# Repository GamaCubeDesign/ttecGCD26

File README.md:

# ttecGCD26 — TT&C, OBC, payload ADS-B e ground station

Repositório da Gama Cube Design para a **CubeDesign 2026**: o software de voo
do Cubetschek (telecomunicação, computador de bordo e payload ADS-B), a
ground station e a documentação de arquitetura.

O hardware: uma Raspberry Pi Zero 2 W a bordo; um rádio LoRa SX1278 (módulo
RA-02) em 433,92 MHz de cada lado do enlace; um SDR NooElec NESDR Nano 3 para
o ADS-B em 1090 MHz; e uma ESP32 DevKit V1 como ground station.

## O número que governa tudo

O enlace LoRa desce **58 KB** nos 10 minutos da missão; 20 aviões geram
**7,34 MiB** de ADS-B bruto no mesmo tempo. É uma diferença de 129 vezes, e
ela obriga o satélite a decodificar e agregar a bordo: ele desce retratos
das aeronaves, com 20 bytes cada, em vez do fluxo bruto. Quase toda a
arquitetura sai daí (`docs/budgets/data-budget.md`, ADR-0003).

## O que tem aqui

| Diretório | O quê | Roda em | Estado em 03/11 |
|---|---|---|---|
| `common/` | O codec compartilhado: frames, CRC, telemetria, telecomandos, IPC, perfis LoRa, o lado da ground do protocolo, os frames do AOCS | Pi, PC **e** ESP32 | pronto |
| `flight/ttcd/` | Telecomunicação: o enlace, os telecomandos, a telemetria; o centro da comunicação entre os processos | Pi | pronto; bancada de 09/10 no protocolo v1 |
| `flight/radio/` | Driver do SX1278 e os rádios real e simulado (UDP) | Pi | pronto |
| `flight/libipc/` | Transporte IPC entre os processos de bordo | Pi | pronto |
| `flight/adsbd/` | Payload ADS-B: supervisiona o `dump1090-fa`, grava o registro de bordo e manda retratos ao `ttcd` | Pi | pronto; com o SDR em 09/10 |
| `flight/obcd/` | Computador de bordo: modos da missão, burn-wire, termostato, sensores da bateria, o I²C emprestado ao AOCS | Pi | pronto; **nunca rodou em hardware** |
| `flight/conf/obc-v2/` | A configuração de voo da placa nova do OBC | Pi | pronta; conferida contra os layouts |
| `ground/console/` | O console da ground station, o mesmo no PC e na ESP32 | Pi, PC, ESP32 | pronto |
| `ground/esp32/` | Firmware da ground station (ESP-IDF, no Docker); `ground/esp32-tests/` roda as suítes portáveis na ESP32 | ESP32 | compila; passa no QEMU; **nunca rodou na placa** |
| `ground/host/` | No PC: a ponte serial da ESP32 (`gs_serial.py`), o adaptador do downlink e o estimador de origem e destino | PC | pronto |
| `tools/` | `gs_cli` (ground de bancada), roteiros da bancada, simulador do `dump1090`, análise, ESP32, CI | Pi, PC | pronto |
| `hardware/` | Fontes KiCad das placas fabricadas e das revisões novas, não fabricadas (`-v2`) | — | — |
| `docs/` | ADRs, orçamentos, ICD do AOCS, requisitos, CDR, relatórios, evidência da bancada | — | — |
| `ultima_missao/` | Código da competição anterior, **congelado**, só referência | — | — |

O software do OBC é escrito aqui desde 20/10/2026. O repositório da outra
equipe (`../obc`) ficou congelado como referência.

## Arquitetura em uma figura

```
 CUBESAT · Raspberry Pi Zero 2 W                              GROUND STATION
 ┌──────────────────────────────────────────────────┐      ┌─────────────────────────┐
 │ [NESDR] ─USB─► dump1090-fa ─TCP :30003 (SBS-1)─┐  │      │ [RA-02] ─SPI─► ESP32    │
 │                                                ▼  │      │   ▲              │ USB  │
 │  adsb.ndjson ◄─ grava ─ adsbd                     │      │   │              ▼      │
 │                          │ IPC                    │      │   │        gs_serial.py │
 │                          ▼                        │      │   │              │ JSON │
 │  [RA-02] ◄─SPI+DIO0─ ttcd ◄──IPC──► obcd          │      │   │              ▼      │
 │     ▲                               │             │      │   │       tracks_to_    │
 │     │      INA219 ◄──I²C1 (dividido)┤             │      │   │       ndjson.py     │
 │     │      ESP32 do AOCS ◄──────────┤             │      │   │              ▼      │
 │     │      DS18B20 ◄─1-Wire─────────┤             │      │   │       estimador e   │
 │     │      burn-wire, aquecedores ◄─┘ GPIO        │      │   │       painel        │
 └─────┼─────────────────────────────────────────────┘      └───┼─────────────────────┘
       └──────────────────── LoRa 433,92 MHz ───────────────────┘
```

- O `ttcd` é o centro: o `adsbd` e o `obcd` se conectam a ele por um socket
  `AF_UNIX`, com os mesmos frames do rádio (ADR-0005, ADR-0006).
- Cada processo tem um núcleo sem chamadas de sistema, testado com relógio
  virtual, e uma casca `epoll` que fala com o sistema operacional.
- O modo da missão, decidido pelo `obcd`, liga a telemetria do `ttcd` e o
  decodificador do `adsbd` (ADR-0014).

O guia de estudo (`docs/relatorios/2026-10-31-guia-de-estudo.html`) explica a
arquitetura, os protocolos e cada arquivo.

## Build e testes

```bash
make                  # configura e compila (CMake, em build/)
make test             # as 38 suítes; make test T=obcd roda só as que casam
make check            # antes de qualquer merge: testes, sanitizers, zero warnings, citações
make check-debian     # o mesmo num contêiner Debian 13, com o GCC 14 da Pi (é o que a CI roda)
make help             # todos os alvos
```

O `make check` roda os testes, compila de novo em `build-asan/` com ASan e
UBSan e com todo warning virando erro, roda os testes ali e confere as
citações de `docs/requisitos.md` contra o regulamento. Na Pi, o segundo build
usa só o UBSan, porque o ASan não inicia no espaço de endereços de 39 bits
dela. Os comandos por baixo (`cmake`, `ctest`, os scripts de `tools/`)
continuam valendo sozinhos.

O build é mantido em **zero warnings** com `-Wall -Wextra -Wpedantic
-Wconversion -Wsign-conversion`. Isso não é cosmético: quase todo bug que este
projeto não pode pagar, um campo de tamanho truncado, um sinal perdido numa
latitude, aparece primeiro como conversão implícita.

A ESP32 compila no Docker, sem instalar o ESP-IDF:

```bash
make esp32-build                          # o firmware da ground
make esp32-tests-qemu                     # as suítes portáveis numa ESP32 emulada
make esp32-flash ESP32_PORT=/dev/ttyUSB0  # grava na placa
```

## Sem hardware, e na bancada

```bash
make bench-ping RADIO=udp                 # um passo da bancada no rádio simulado
make adsb-chain INPUT=<captura.sbs|registro.ndjson>   # uma missão inteira pela cadeia
```

- Para mandar o código do PC para a Pi, os passos da bancada dos rádios e a
  instalação dos serviços, veja `flight/ttcd/README.md`.
- O roteiro da próxima bancada é
  `docs/relatorios/2026-11-03-roteiro-bancada.html`.
- A evidência das bancadas fica em `docs/vv/bancada/`.

## Orçamento de enlace e de dados

Todo número citado nos ADRs sai de um script:

```bash
make budget           # as tabelas completas (tools/analysis/lora_budget.py)
make budget-check     # confere contra os ADRs (também roda no make test)
make boards           # a configuração de voo conferida, fio a fio, contra os layouts das placas
```

## Onde começar a ler

1. `AGENTS.md`: as regras do repositório, o mapa e o estado corrente.
2. O guia de estudo, `docs/relatorios/2026-10-31-guia-de-estudo.html`: do
   conceito ao arquivo.
3. `docs/adr/README.md`: o índice das decisões. Comece pelo ADR-0003 (por que
   o processamento é a bordo) e pelo ADR-0004 (a configuração do rádio, com a
   aritmética).
4. `PLANO.md`: o plano até a prova, as decisões, as questões em aberto e os
   riscos.
5. `docs/requisitos.md`: cada requisito citado literalmente, com o estado.

Os relatórios de estado, datados, ficam em `docs/relatorios/`; o mais recente
é `2026-11-03-status-firmware.html`.

## Convenções

- **Código e comentários: inglês.** ADRs, ICDs e orçamentos também: o
  regulamento (§2) exige o Design Package em inglês, e esses documentos entram
  nele quase literalmente.
- **READMEs, PLANO e notas de trabalho: português.**
- Identificadores de requisito (`HLR-ADS-07` etc.) são citados em comentário
  no ponto do código que os atende; a matriz de rastreabilidade sai daí.
- Nunca serializar struct por cast. Todo campo multi-byte passa pelos helpers
  little-endian de `common/gama_bytes.h`. O porquê está no ADR-0002.

## `ultima_missao/`

O código da competição anterior, **congelado**, mantido só como referência.
O que foi reaproveitado e o que foi descartado está nos ADRs 0002 e 0004, com
o motivo de cada descarte. Os defeitos dele viraram as "regras duras" do
`AGENTS.md`.

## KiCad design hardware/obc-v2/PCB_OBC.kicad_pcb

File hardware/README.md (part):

# Placas do Cubetschek — fontes KiCad

As placas como foram **fabricadas**: as fontes dos dois painéis enviados à
Circuibras em 08/10/2026, trazidas de `PCBS_GCD_Com_Paineis.zip` em
22/10/2026. Uma pasta por placa; cada uma abre no KiCad pelo `.kicad_pro`
(os painéis exigem o KiCad 10). As exceções são as pastas `-v2`, que ainda
não foram fabricadas: `obc-v2/`, a placa nova do OBC, e `eps-potencia-v2/` e
`aocs-v2/`, da revisão TF de 01–02/11 (abaixo). A `antenas/` veio de outro
zip, `PCB_mec.7z` (abaixo).

| Pasta | Placa | Observação |
|---|---|---|
| `obc/` | OBC: Raspberry Pi Zero 2 W, INA219, barramento | revisão de 08/10 (`PCB_NOVAS_REVISADAS/PCB_OBC_NOVA`); esquemático e layout **divergem** no I²C (pinos 10 e 12); a `obc-v2/` a substitui |
| `obc-v2/` | OBC, placa nova | esquemático de 23/10 (`PCB_OBC_NEW.zip`), layout da revisão TF de 02/11; **não fabricada**; corrige A1, A2, A3 e A7 |
| `ttec/` | TT&C: Ra-02, USB do SDR, J4 (JST XH) do burn-wire, para a placa de antenas | bibliotecas locais em `Library.pretty/` e `lib.sym/` |
| `eps-potencia/` | EPS: BMS 2S, conversores de 5 V, 3,3 V e 12 V, entrada externa | revisão de 08/10 (`PCB_NOVAS_REVISADAS/PCB_EPS_EXTRA_NOVA`) |
| `eps-potencia-v2/` | EPS, revisão TF | layout de 02/11, **mesmas ligações** da fabricada; sem esquemático; **não fabricada** |
| `bateria-cima/` | bateria de cima: 18650, aquecedores, TIP120, DS18B20 | |
| `bateria-baixo/` | bateria de baixo: 18650, aquecedores, TIP120 | sem sensor de temperatura |
| `aocs/` | AOCS: ESP32, BMI088, AS5048A, DRV8313 | o esquemático estava em `AOCS/grb/` no zip |
| `aocs-v2/` | AOCS, revisão TF | layout de 02/11, **mesmas ligações** do fabricado; sem esquemático; **não fabricado** |
| `painel-solar-1/`, `painel-solar-2/` | painéis solares | |
| `topo/` | tampa superior | só logotipos, sem componentes |
| `paineis/` | os dois painéis de fabricação, 20 placas cada | ver abaixo |
| `antenas/` | placa de antenas: dipolo de fitas do LoRa, dipolo impresso do ADS-B, os baluns LC e o burn-wire (TIP120), que é a placa do mecanismo | KiCad de 19/10 (`PCB_mec.7z`) e `componentes_baluns.pdf` (valores comerciais dos baluns, co-simulação HFSS); fabricação a confirmar |

A placa do **mecanismo** (burn-wire) é a de antenas: seção `antenas/`, abaixo.

As revisões de 08/10 do OBC e da EPS são as que foram para os painéis
(conferido pelo SHA-256 citado em `paineis/Relatorio_Painelizacao.md`). As
versões anteriores, que ficavam em `OBC/` e `EPS/` no zip, não foram
fabricadas e ficaram de fora. A revisão não mudou nenhuma ligação do
barramento de 40 pinos nas duas placas.

## `obc-v2/` — a placa nova do OBC

O esquemático de `PCB_OBC_NEW.zip` (KiCad de 23/10/2026), a pinagem em uso
desde 31/10, com o layout da revisão TF de 02/11 (seção seguinte; o layout
de 23/10 fica no histórico do git, commit `99adcf1`). Ficaram de fora o
`.history/` e o `.kicad_prl`. Conferida pelo netlist do esquemático e pelos
pads do `.kicad_pcb`, que concordam.

Dos achados de `docs/relatorios/2026-10-22-validacao-obc.html`, corrige:

| Achado | Na placa nova |
|---|---|
| A1: o 8 V passava pelo INA219 em pinos que a EPS não usa | entra do 8 V Bruto no J1.38, onde a EPS o põe, e sai no J1.33; o J1.35 ficou livre |
| A2: o barramento do LoRa trocado com o da TT&C | J1.21 SCK, 23 MISO, 25 MOSI, 27 NSS, 29 RESET, 31 DIO0, como o J3 da TT&C |
| A3: SDA e SCL trocados no layout | J1.10 SDA, J1.12 SCL, como o AOCS |
| A7: DS18B20 sem pull-up | R1, 4,7 kΩ, do 3,3 V à linha do DS18B20 (GPIO17, J1.9) |

Não muda:

- **A5 e A6:** R2 e R3 continuam 4,7 kΩ entre o GPIO e a base dos TIP120
  (GPIO22 → J1.13, burn-wire; GPIO23 → J1.11, aquecedores). Nos aquecedores
  são ~0,43 mA para duas bases. No burn-wire, o R2 fica em série com o 220 Ω
  e o pull-down de 10 kΩ da placa de antenas: ~0,25 mA de base, ~0,25 A
  garantidos com o ganho mínimo de 1000 do TIP120, contra o ~1 A do ensaio
  do CDR. Com o R2 em 470 Ω, a base recebe ~2,6 mA e o TIP120 satura.
- **O INA219 fica no I²C1**, dividido com o ESP32 do AOCS (GPIO2/3, J1.10 e
  J1.12): a proposta de 24/10 de levá-lo ao I²C0 não entrou. O `obcd`
  empresta o barramento ao ESP32 durante o `ADVANCED_AOCS` (ADR-0017).

Pinos da Pi nesta placa:

| Função | GPIO | Barramento (J1) |
|---|---|---|
| LoRa SCK, MISO, MOSI, NSS | 11, 9, 10, 8 (SPI0, CE0) | 21, 23, 25, 27 |
| LoRa RESET, DIO0 | 25, 4 | 29, 31 |
| I²C1 SDA, SCL: INA219 (0x40) e ESP32 do AOCS | 2, 3 | 10, 12 |
| DS18B20 (1-Wire) | 17 | 9 |
| burn-wire, aquecedores (bases dos TIP120) | 22, 23 | 13, 11 |

Com o DIO0 no GPIO4, que é o pino padrão do 1-Wire, o `config.txt` precisa
de `dtoverlay=w1-gpio,gpiopin=17`. A configuração do software para esta
placa está em `flight/conf/obc-v2/`.

## `antenas/` — a placa de antenas e o burn-wire

`PCB_mec.7z`, recebido em 03/11: o projeto `PCB_antenas` da equipe de
antenas, KiCad de 19/10. A placa leva o dipolo de fitas do LoRa (face de
cima), o dipolo impresso do ADS-B (face de baixo) e os baluns LC dos dois.
Desde 19/10 leva também o circuito do burn-wire: é a placa do mecanismo. O
`componentes_baluns.pdf` já estava na pasta.

O burn-wire é o circuito da Figura 15 do CDR:

| JST1 (JST EH) | Na placa de antenas | J4 da TT&C (JST XH) |
|---|---|---|
| 1 | `GND_q`: emissor do TIP120 (Q1) e R1 | GND |
| 2 | furo H14: uma ponta do NiCr | +5V, do J3.15 |
| 3 | R2, 220 Ω, até a base do Q1 | o sinal do J3.13 (GPIO22, pelo R2 de 4,7 kΩ do OBC) |

- R1, de 10 kΩ, vai da base ao emissor: é o pull-down que o achado A8 pedia.
  A outra ponta do NiCr vai no furo H15, o coletor. O NiCr é soldado nos
  furos H14 e H15 (0,8 mm, não metalizados, com anel nas duas faces).
- O cabo liga o J4 ao JST1 pino a pino. XH e EH têm o mesmo passo, mas não
  são intercambiáveis: o cabo leva um alojamento de cada série.
- O ensaio do CDR (§6.4) tinha esse circuito sem o R2 de 4,7 kΩ do OBC:
  ~8,5 mA de base, 1 A a 5 V, pulso de 2 s. Com o 4,7 kΩ em série,
  ~0,25 mA (A5, abaixo).

O DRC (`kicad-cli pcb drc --schematic-parity`) dá 0 violações das regras da
placa (folga de 0,15 mm), 1 aviso de serigrafia e 0 divergências entre o
esquemático e o layout. Os 3 itens "desconectados" são as ligações por fio
soldado à mão, de propósito: o H10, que representa o GND das duas faces
(ligado pelos furos H9–H13), e o H14 e o H15, as pontas do NiCr.

Ficaram de fora o `.history/` e o `.kicad_prl`. Também ficaram de fora, por
serem de 14/10, de antes do burn-wire, a pasta `fabricacao/` (gerbers,
furação, BOM, posição, PDFs, STEP), as `imagens/` e o `README.md` do projeto.
A furação de lá só tem os 4 furos das fitas, e o BOM só os componentes de
RF: os arquivos de fabricação precisam ser gerados de novo a partir do
`.kicad_pcb`. Os `scripts/` que geram a placa a partir do DXF do HFSS (que
não veio no zip) também ficaram de fora: eles não têm o burn-wire, e rodá-los
de novo apaga o circuito.

## A revisão TF (01–02/11/2026)

`PCBS_GAMA_AOCS_EPS1_OBC_TF.zip`, recebido em 03/11: novos layouts do OBC, da
EPS e do AOCS. **Nenhuma ligação mudou.** Comparados pad a pad, pela net de
cada pad no `.kicad_pcb` (`tools/analysis/board_check.py diff`):

- o OBC TF contra o `obc-v2` de 23/10: 0 mudanças; esquemático, `.kicad_pro`
  e `.kicad_dru` idênticos byte a byte;
- a EPS TF contra a `eps-potencia/` fabricada: 0 mudanças;
- o AOCS TF contra o `aocs/` fabricado: 0 mudanças.

O que mudou é o cobre:

| Placa | Trilhas | Vias | Componentes |
|---|---|---|---|
| OBC | re-roteadas, todas de 1 mm: 258 → 206 segmentos | 40 → 33 | nenhum se moveu |
| EPS | todas de 1 mm, como antes: 107 → 98 segmentos | 343 → 37 | a chave SW1 desceu ~7 mm; furos renumerados |
| AOCS | de 0,5 para 1 mm: 115 → 157 segmentos | 391 → 47 | furos renumerados |

O contorno (83 × 83 mm) e os conectores do barramento estão no mesmo lugar:
o empilhamento não muda.

**O DRC do KiCad** (`kicad-cli pcb drc`) não acha nenhum item desconectado
nem curto nas três, mas acha erros que as versões anteriores não tinham. São
para resolver antes de fabricar:

- **OBC:** 5 violações da regra própria `caseira_isolacao_1mm`, com 0,86 a
  0,99 mm de folga. Os pares são as vias DIO0 × NSS e a trilha MOSI × a via
  MISO, do LoRa, e as vias TIP120(CT) × DS18B20. Há também 2 pontas de
  trilha soltas (SCL e DIO0). O `PCB_OBC.kicad_dru` tem dois conjuntos de
  regras: as da Circuibras (folga de 0,127 mm), em que o OBC TF passa, e, no
  fim, as da versão caseira (transferência térmica: folga e trilha de 1 mm),
  que valem por cima. A reunião de 03/11 decidiu que o OBC é feito pela
  equipe, que é justamente o caso da regra caseira. Falta confirmar que o
  processo separa 0,86 mm, e baixar a regra para esse valor, ou afastar os
  três pontos.
- **AOCS:** a trilha do D34 do ESP32 passa a 0,24 mm do pad de GND do
  conector X+, contra os 0,5 mm da classe padrão; a Circuibras faz 0,127 mm,
  então depende de quem fabrica. Há também 6 trilhas com uma
  ponta solta (três delas de ~22 mm, nas entradas IN1–IN3 do DRV8313) e duas
  vias empilhadas no mesmo ponto, no SDA do BMI088.
- **EPS:** só avisos de serigrafia e de footprint.

**Como entraram.** A EPS e o AOCS vieram sem esquemático: o da EPS estava
vazio e ficou de fora, porque um "Update PCB from Schematic" com ele apagaria
todos os componentes. O esquemático que vale para os dois é o da versão
fabricada (`eps-potencia/`, `aocs/`), já que as ligações são as mesmas. O
projeto do AOCS se chamava `AAAAAAAAAAAAAAAAAAAAAAAAAAAAA` no zip e foi
renomeado para `AOCS_TF`. Os footprints estão embutidos nos `.kicad_pcb`; a
biblioteca do AOCS continua em `aocs/`. Os modelos 3D apontam para caminhos
nos computadores dos autores, como nas versões fabricadas.

## O firmware e as pendências de 22/10

`python3 tools/analysis/board_check.py` segue cada fio que o firmware usa, do
GPIO da Pi ao pino do chip na outra placa. Ele lê os layouts do stack
(`obc-v2`, `ttec`, `eps-potencia-v2`, as baterias e `aocs-v2`), a placa de
antenas, ligada à TT&C por um cabo, e a configuração em
`flight/conf/obc-v2/`. Em 03/11 passa em todas as 20 conferências, e roda no
`make test`. Item a item de
`docs/relatorios/2026-10-22-validacao-obc.html`:

| Achado | Nas placas | O firmware |
|---|---|---|
| A1 · 8 V pelo INA219 | corrigido no OBC: entra do 8V(Bruto) da EPS no J1.38, sai no J1.33 para o 8V(Liq) | nada a mudar. Sem a placa do OBC no stack, nada recebe energia (HLR-EPS-05) |
| A2 · barramento do LoRa | corrigido: 21–31 casam com o J3 da TT&C | `ttcd.conf` confere: `spidev0.0`, RESET 25, DIO0 4 |
| A3 · SDA e SCL | corrigido: 10 SDA, 12 SCL no OBC e no AOCS | `obcd.conf` confere: `/dev/i2c-1` |
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
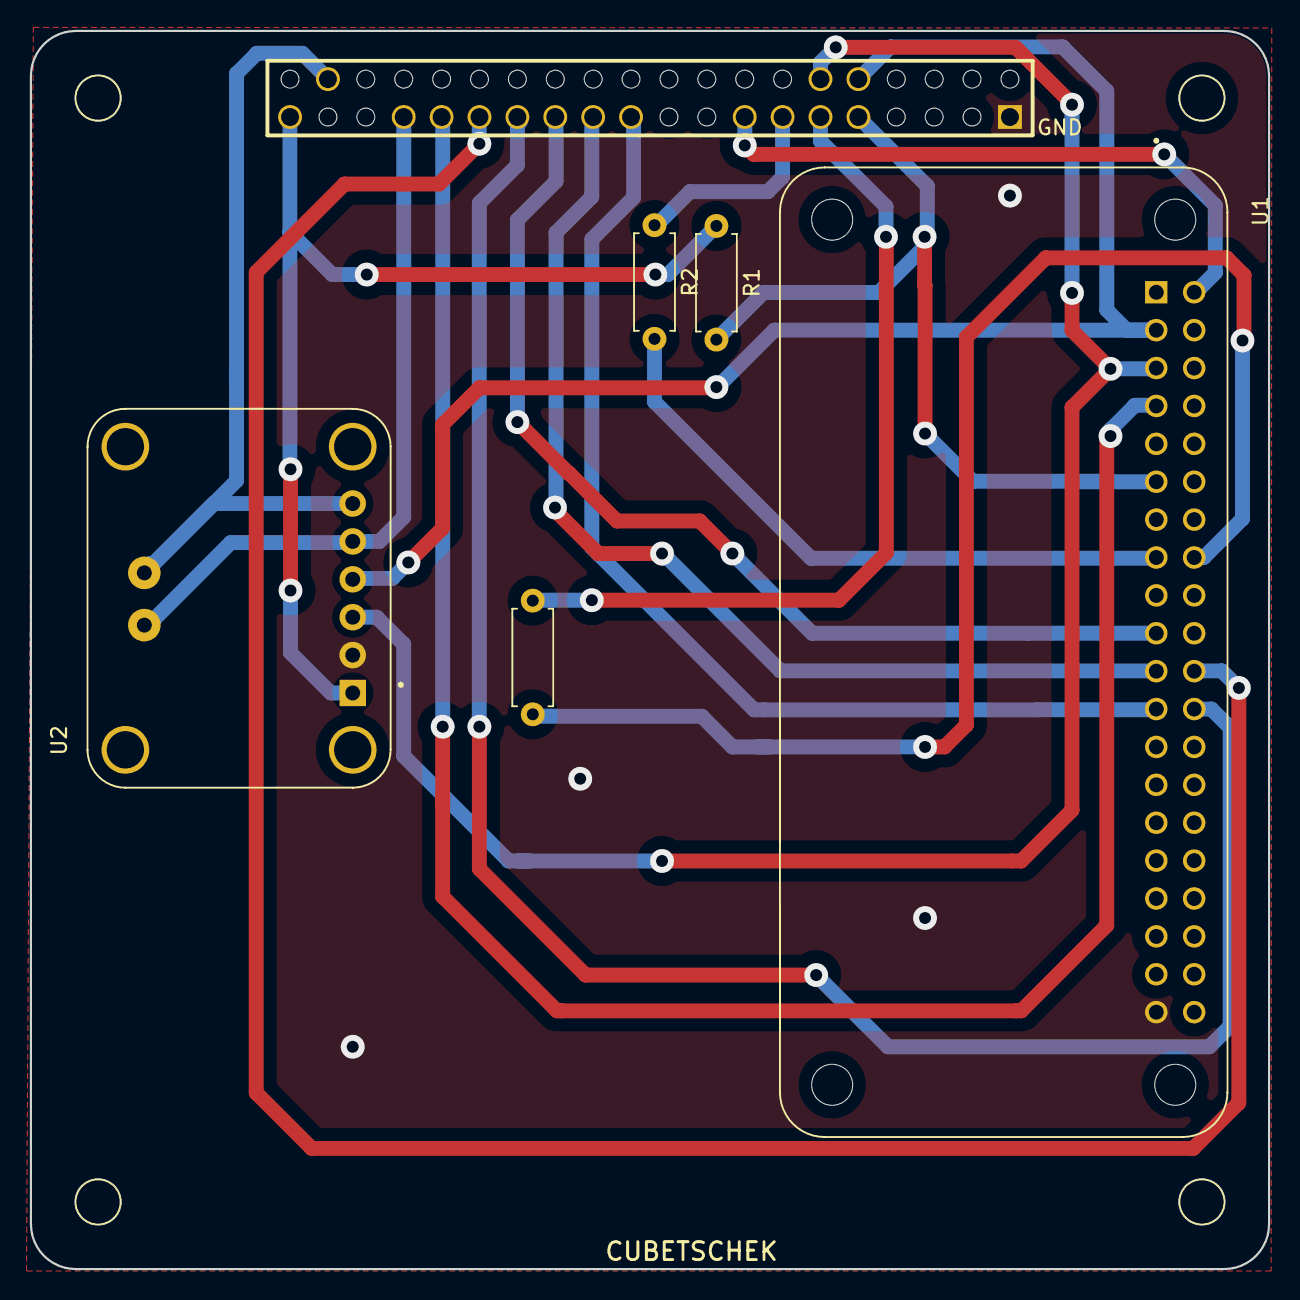
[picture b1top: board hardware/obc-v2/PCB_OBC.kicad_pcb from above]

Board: 2 copper layers, 83.0 x 83.0 mm, 6 parts (0 on the bottom side), 18 nets.

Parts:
J1: PC104_PSTD-2.54-2X20P
R1, R2, R3: 4.7k; R_Axial_DIN0207_L6.3mm_D2.5mm_P7.62mm_Horizontal
U1: RASPBERRY_PI_ZERO_2_W; MODULE_RASPBERRY_PI_ZERO_2_W
U2: INA219; MODULE_INA219

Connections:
/3V3: J1.39, R1.1, U2.1 (VCC)
/5V: J1.15, U1.2 (5V_2)
/8V Bruto: J1.38, U2.6 (VIN+), U2.VIN+
/8V(INA): J1.33, U2.5 (VIN-), U2.VIN-
/DIO0 LORA: J1.31, U1.7 (GPIO4/GPIO_GCLK)
/DS18B20: J1.9, R1.2, U1.11 (GPIO17/GPIO_GEN0)
/GND: J1.1, U1.39 (GND_39), U2.2 (GND)
/MISO LORA: J1.23, U1.21 (GPIO9/SPI_MISO)
/MOSI LORA: J1.25, U1.19 (GPIO10/SPI_MOSI)
/NSS LORA: J1.27, U1.24 (GPIO8/SPI_~CE0)
/RESET LORA: J1.29, U1.22 (GPIO25/GPIO_GEN6)
/SCK LORA: J1.21, U1.23 (GPIO11/SPI_SCLK)
/SCL: J1.12, U1.5 (GPIO3/SCL), U2.3 (SCL)
/SDA: J1.10, U1.3 (GPIO2/SDA1), U2.4 (SDA)
/TIP120(CT): J1.11, R3.2
/TIP120(Mec): J1.13, R2.1
unnamed: R2.2, U1.15 (GPIO22/GPIO_GEN3)
unnamed: R3.1, U1.16 (GPIO23/GPIO_GEN4)

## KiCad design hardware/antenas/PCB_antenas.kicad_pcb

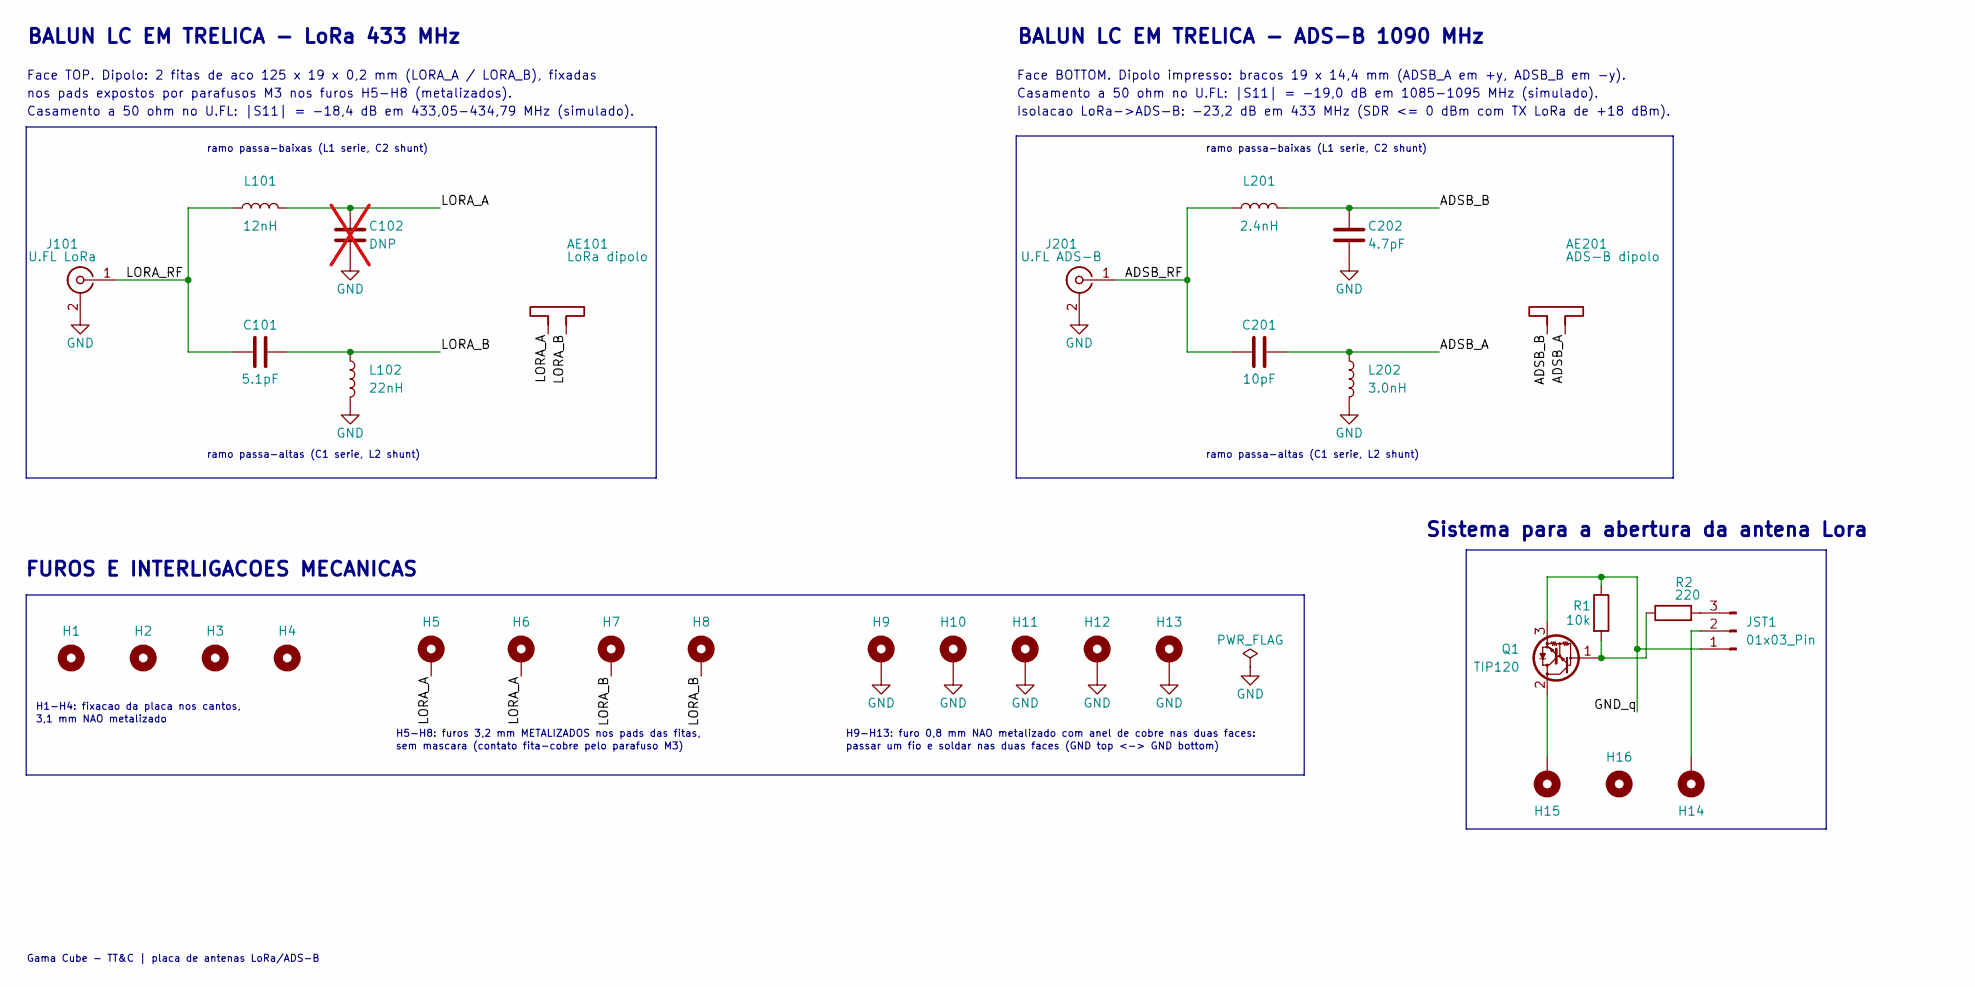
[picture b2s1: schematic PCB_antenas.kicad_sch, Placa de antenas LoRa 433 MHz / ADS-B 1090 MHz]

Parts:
AE101: LoRa dipolo
AE201: ADS-B dipolo
C101: 5.1pF; C_0402_1005Metric
C102: DNP; C_0402_1005Metric; not fitted
C201: 10pF; C_0603_1608Metric
C202: 4.7pF; C_0603_1608Metric
H1, H2, H3, H4, H16: Furo 3,1 NPTH; Furo_Fixacao_3.1mm_NPTH
H5, H6, H7, H8: Furo fita 3,2 PTH; Furo_Fita_3.2mm_PTH
H9, H10, H11, H12, H13, H14, H15: Fio GND; Furo_Fio_GND_0.8mm
J101: U.FL LoRa; U.FL_Hirose_U.FL-R-SMT-1_Vertical_SemJanela
J201: U.FL ADS-B; U.FL_Hirose_U.FL-R-SMT-1_Vertical_SemJanela
JST1: 01x03_Pin; JST_EH_B3B-EH-A_1x03_P2.50mm_Vertical
L101: 12nH; L_0603_1608Metric
L102: 22nH; L_0603_1608Metric
L201: 2.4nH; L_0402_1005Metric
L202: 3.0nH; L_0603_1608Metric
Q1: TIP120; TO-220-3_Vertical
R1: 10k; R_Axial_DIN0207_L6.3mm_D2.5mm_P7.62mm_Horizontal
R2: 220; R_Axial_DIN0207_L6.3mm_D2.5mm_P7.62mm_Horizontal

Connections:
/ADSB_A: AE201.2, C201.2, L202.1
/ADSB_B: AE201.1, C202.1, L201.2
/ADSB_RF: C201.1, J201.1 (In), L201.1
/GND_q: JST1.1, Q1.3 (E), R1.1
/LORA_A: AE101.1, C102.1, H5.1 (1_1), H6.1 (1_1), L101.2
/LORA_B: AE101.2, C101.2, H7.1 (1_1), H8.1 (1_1), L102.1
/LORA_RF: C101.1, J101.1 (In), L101.1
GND: C102.2, C202.2, H9.1 (1_1), H10.1 (1_1), H11.1 (1_1), H12.1 (1_1), H13.1 (1_1), J101.2 (Ext), J201.2 (Ext), L102.2, L202.2
unnamed: H14.1 (1_1), JST1.2
unnamed: JST1.3, R2.2
unnamed: Q1.1 (B), R1.2, R2.1
unnamed: H15.1 (1_1), Q1.2 (C)

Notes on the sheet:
H1-H4: fixacao da placa nos cantos,
BALUN LC EM TRELICA - ADS-B 1090 MHz
ramo passa-altas (C1 serie, L2 shunt)
FUROS E INTERLIGACOES MECANICAS
Isolacao LoRa->ADS-B: -23,2 dB em 433 MHz (SDR <= 0 dBm com TX LoRa de +18 dBm).
Gama Cube - TT&C | placa de antenas LoRa/ADS-B
Casamento a 50 ohm no U.FL: |S11| = -18,4 dB em 433,05-434,79 MHz (simulado).
ramo passa-baixas (L1 serie, C2 shunt)
passar um fio e soldar nas duas faces (GND top <-> GND bottom)
Face TOP. Dipolo: 2 fitas de aco 125 x 19 x 0,2 mm (LORA_A / LORA_B), fixadas
sem mascara (contato fita-cobre pelo parafuso M3)
H5-H8: furos 3,2 mm METALIZADOS nos pads das fitas,
Face BOTTOM. Dipolo impresso: bracos 19 x 14,4 mm (ADSB_A em +y, ADSB_B em -y).
nos pads expostos por parafusos M3 nos furos H5-H8 (metalizados).
Casamento a 50 ohm no U.FL: |S11| = -19,0 dB em 1085-1095 MHz (simulado).
3,1 mm NAO metalizado
BALUN LC EM TRELICA - LoRa 433 MHz
H9-H13: furo 0,8 mm NAO metalizado com anel de cobre nas duas faces:
Sistema para a abertura da antena Lora

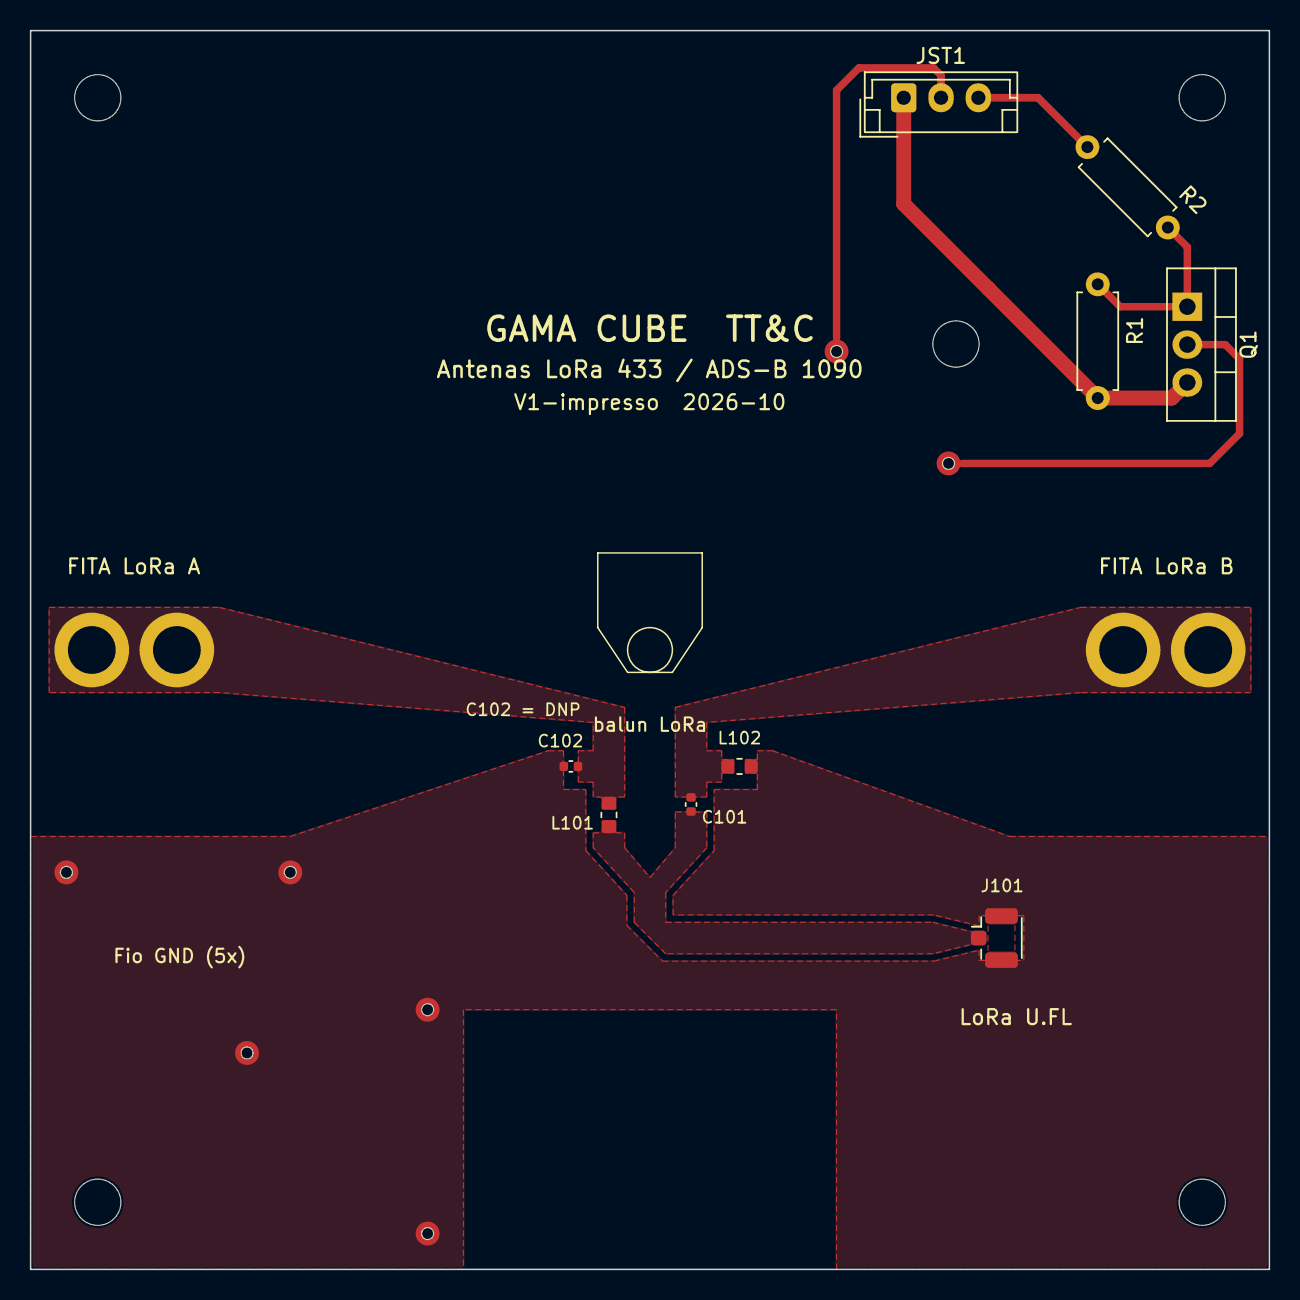
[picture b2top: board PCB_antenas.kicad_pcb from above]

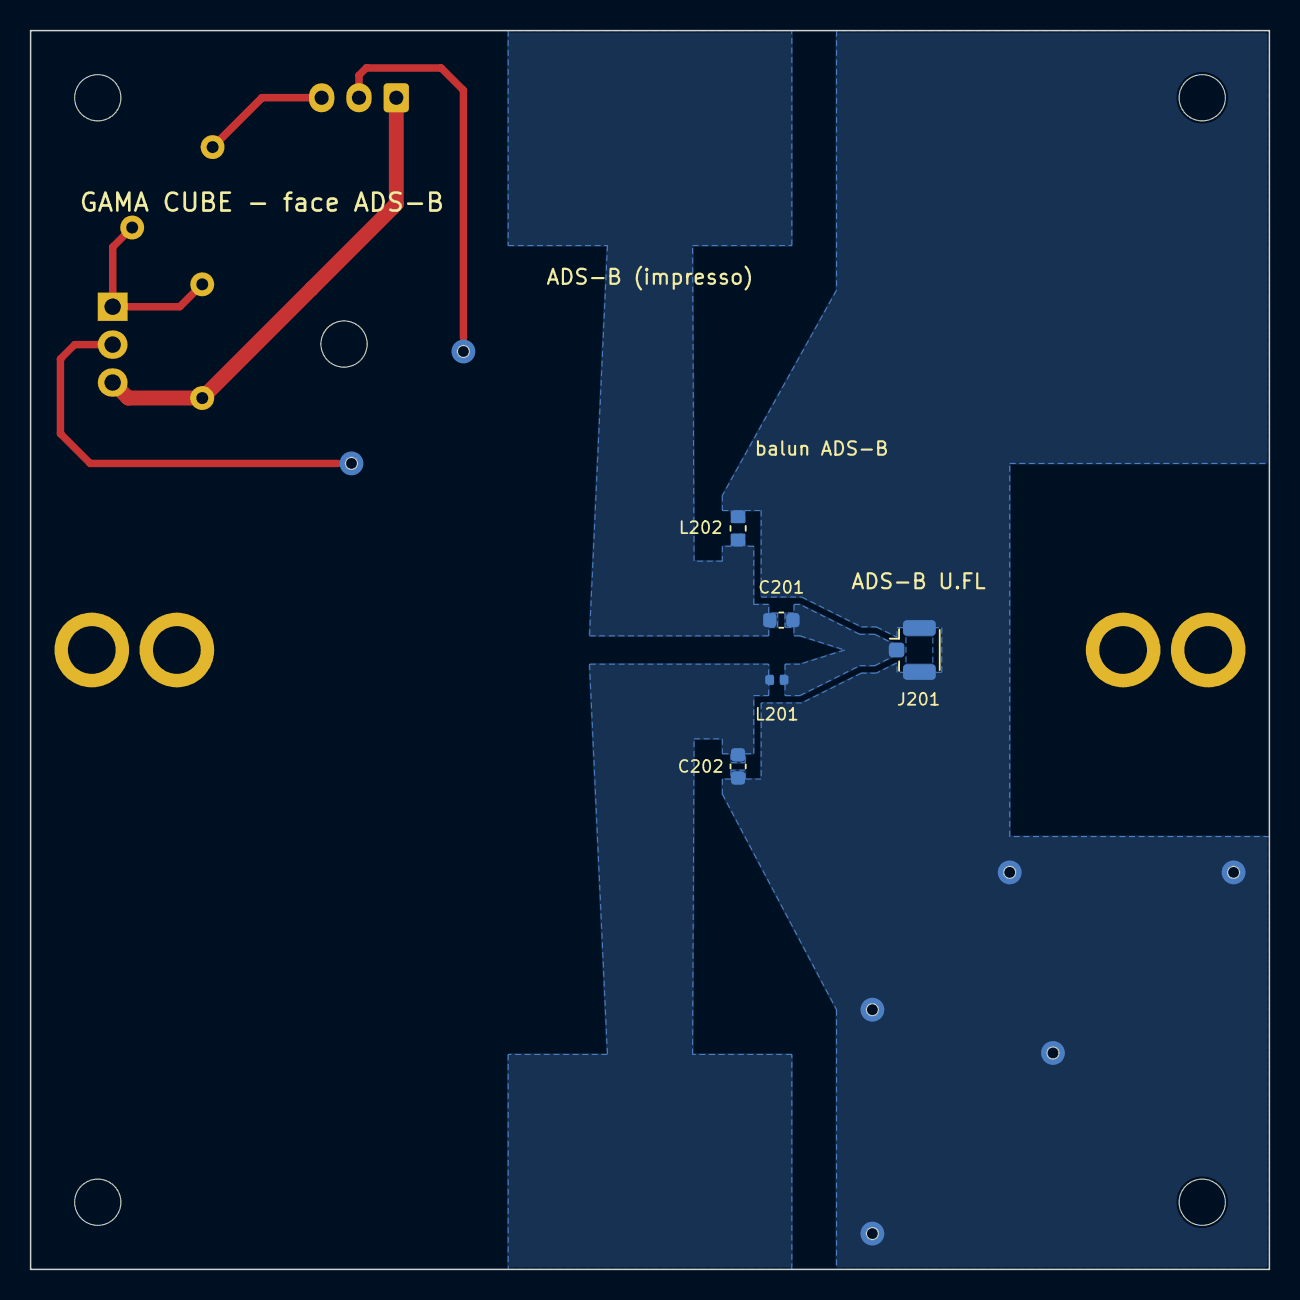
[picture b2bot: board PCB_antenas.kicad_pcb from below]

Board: 2 copper layers, 83.0 x 83.0 mm, 30 parts (5 on the bottom side), 12 nets.

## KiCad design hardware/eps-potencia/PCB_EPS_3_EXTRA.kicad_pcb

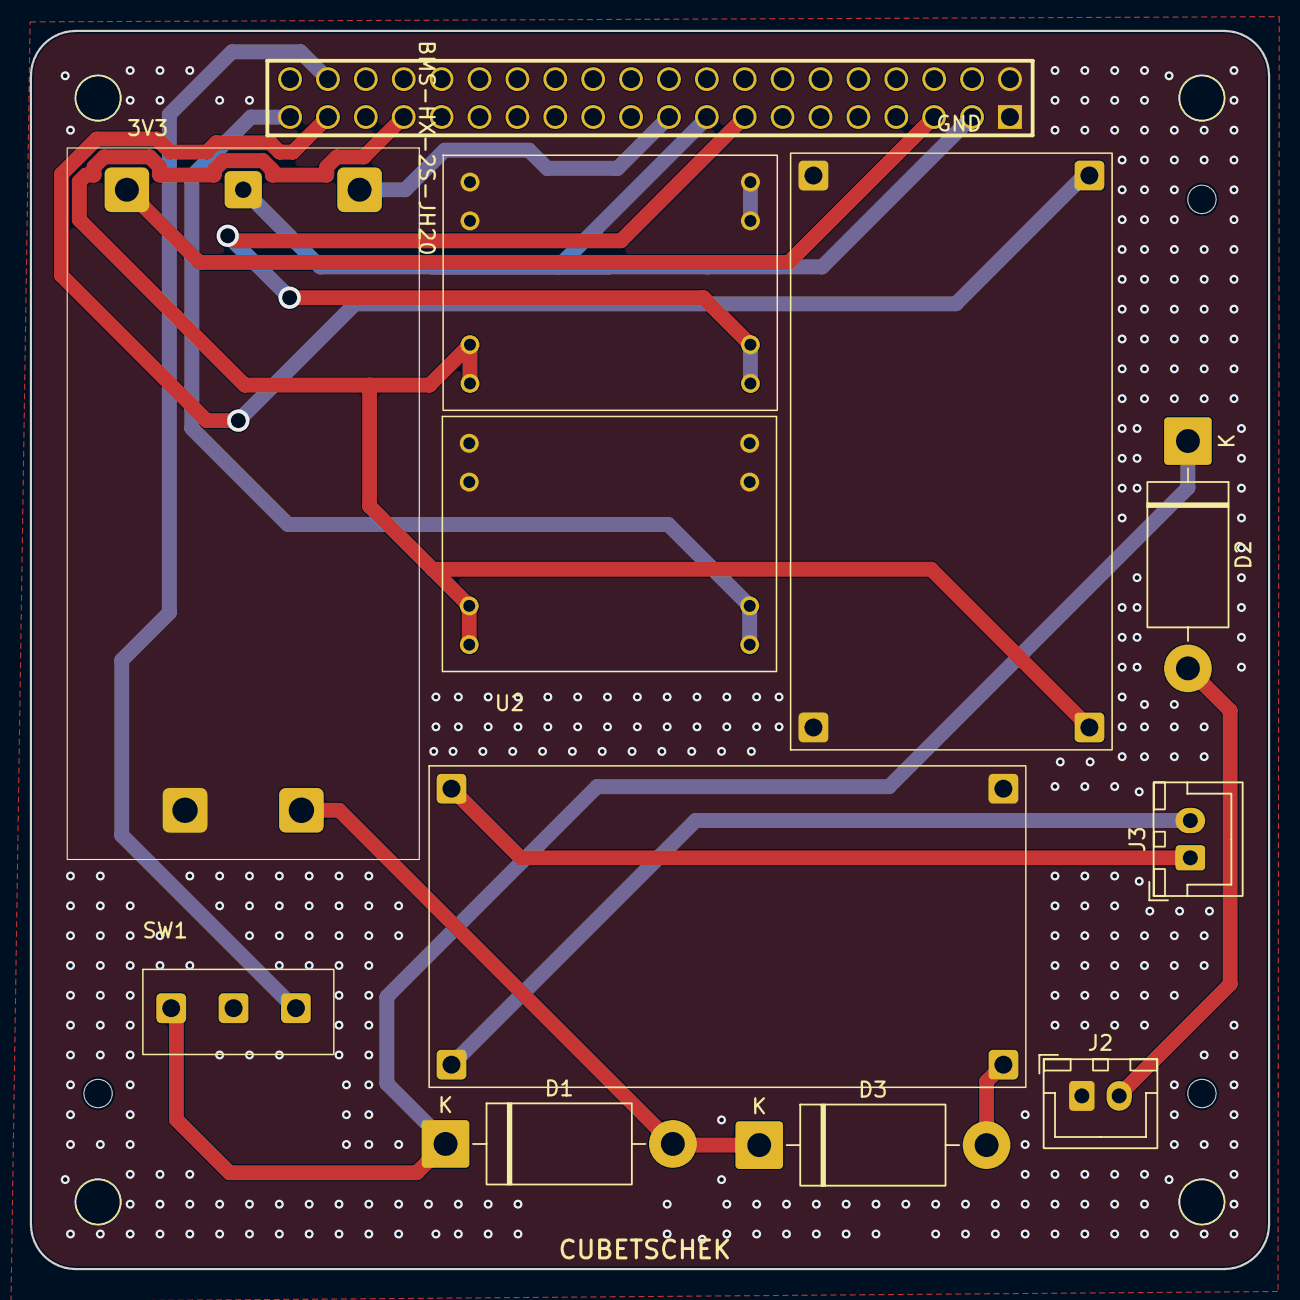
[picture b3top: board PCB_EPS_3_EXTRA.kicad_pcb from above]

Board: 2 copper layers, 83.0 x 83.0 mm, 12 parts (0 on the bottom side), 15 nets.

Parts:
BMS-HX-2S-JH20: HX-2S-JH20
D1, D2, D3: 1N5822; D_DO-201AD_P15.24mm_Horizontal
J1: Conn_02x20_Odd_Even; PC104_PSTD-2.54-2X20P
J2, J3: Conn_01x02_Pin; JST_XH_B2B-XH-A_1x02_P2.50mm_Vertical
MP1584_Module1, MP1584_Module2: MP1584_MODULE
SW1: SW_SPDT; KW10
U1, U2: TPS61088

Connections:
/3V3: J1.39, MP1584_Module2.4 (VOUT+)
/5V: J1.15, MP1584_Module1.4 (VOUT+)
/8V(Bruto): J1.38, SW1.1 (A)
/8V(Liq): J1.33, MP1584_Module1.1 (VIN+), MP1584_Module2.1 (VIN+), U1.1 (VIN+)
/12V: J1.37, U1.4 (VOUT+)
/GND: BMS-HX-2S-JH20.5 (P-), J1.1, J1.2, J2.1, MP1584_Module1.2 (VIN-), MP1584_Module1.3 (VOUT-), MP1584_Module2.2 (VIN-), MP1584_Module2.3 (VOUT-), U1.2 (VIN-), U1.3 (VOUT-), U2.3 (VOUT-)
/Negativo Bateria Inf: BMS-HX-2S-JH20.3 (B-), J1.5
/Negativo Bateria Sup: BMS-HX-2S-JH20.2 (BM), J1.3, J1.17
/Positivo Bateria Sup: BMS-HX-2S-JH20.1 (B+), J1.19
unnamed: BMS-HX-2S-JH20.4 (P+), D1.2 (A), D3.1 (K)
unnamed: D1.1 (K), D2.1 (K), SW1.3 (C)
unnamed: D2.2 (A), J2.2
unnamed: D3.2 (A), U2.4 (VOUT+)
unnamed: J3.1, U2.2 (VIN-)
unnamed: J3.2, U2.1 (VIN+)

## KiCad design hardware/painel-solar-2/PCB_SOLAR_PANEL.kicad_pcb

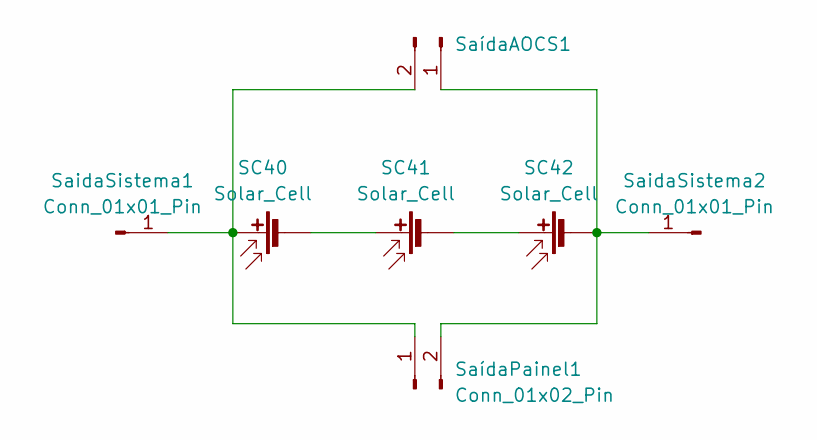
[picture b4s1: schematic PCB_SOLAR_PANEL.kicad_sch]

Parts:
SC40, SC41, SC42: Solar_Cell; Solar_Panel_45mm
SaidaSistema1, SaidaSistema2: Conn_01x01_Pin; PinSocket_1x01_P2.54mm_Vertical
SaídaAOCS1: Conn_01x02_Pin; JST_EH_B2B-EH-A_1x02_P2.50mm_Vertical
SaídaPainel1: Conn_01x02_Pin; JST_EH_B2B-EH-A_1x02_P2.50mm_Vertical

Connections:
unnamed: SC40.1 (+), SaidaSistema1.1 (Pin_1_1), SaídaAOCS1.2, SaídaPainel1.1
unnamed: SC40.2 (-), SC41.1 (+)
unnamed: SC41.2 (-), SC42.1 (+)
unnamed: SC42.2 (-), SaidaSistema2.1 (Pin_1_1), SaídaAOCS1.1, SaídaPainel1.2

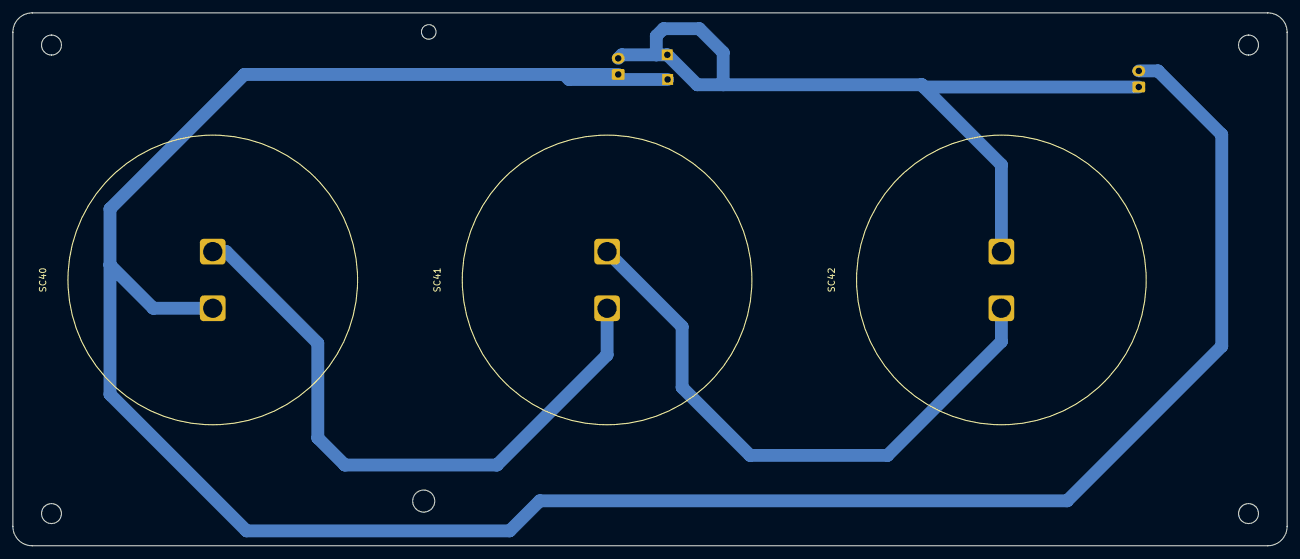
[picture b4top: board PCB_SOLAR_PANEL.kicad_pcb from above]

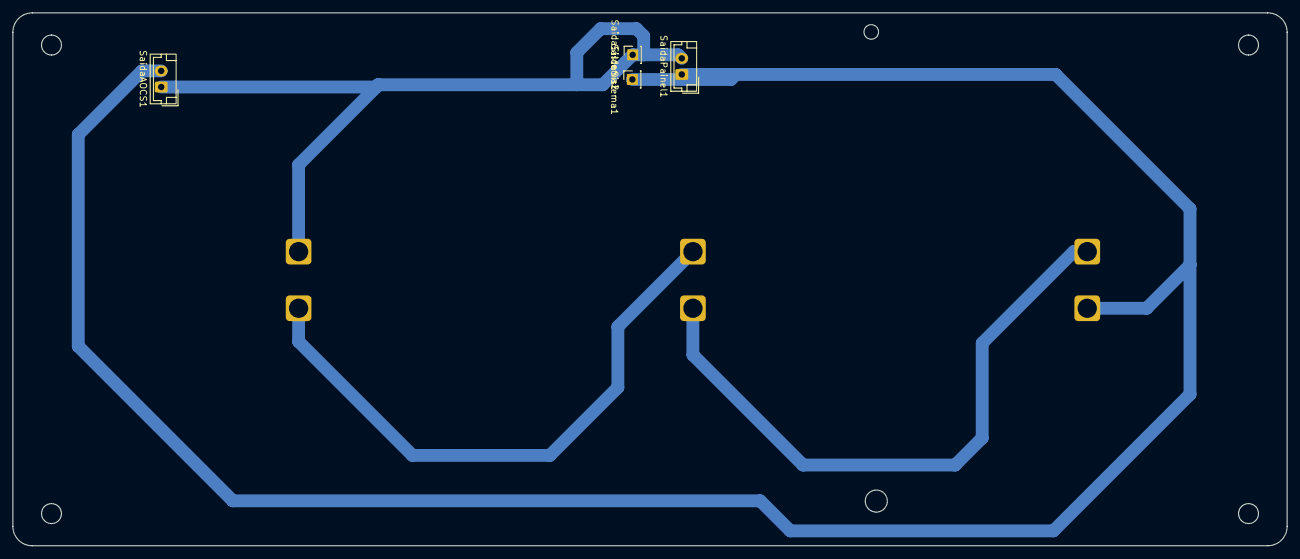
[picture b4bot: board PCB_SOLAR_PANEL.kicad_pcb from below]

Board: 2 copper layers, 198.0 x 82.8 mm, 7 parts (4 on the bottom side), 4 nets.

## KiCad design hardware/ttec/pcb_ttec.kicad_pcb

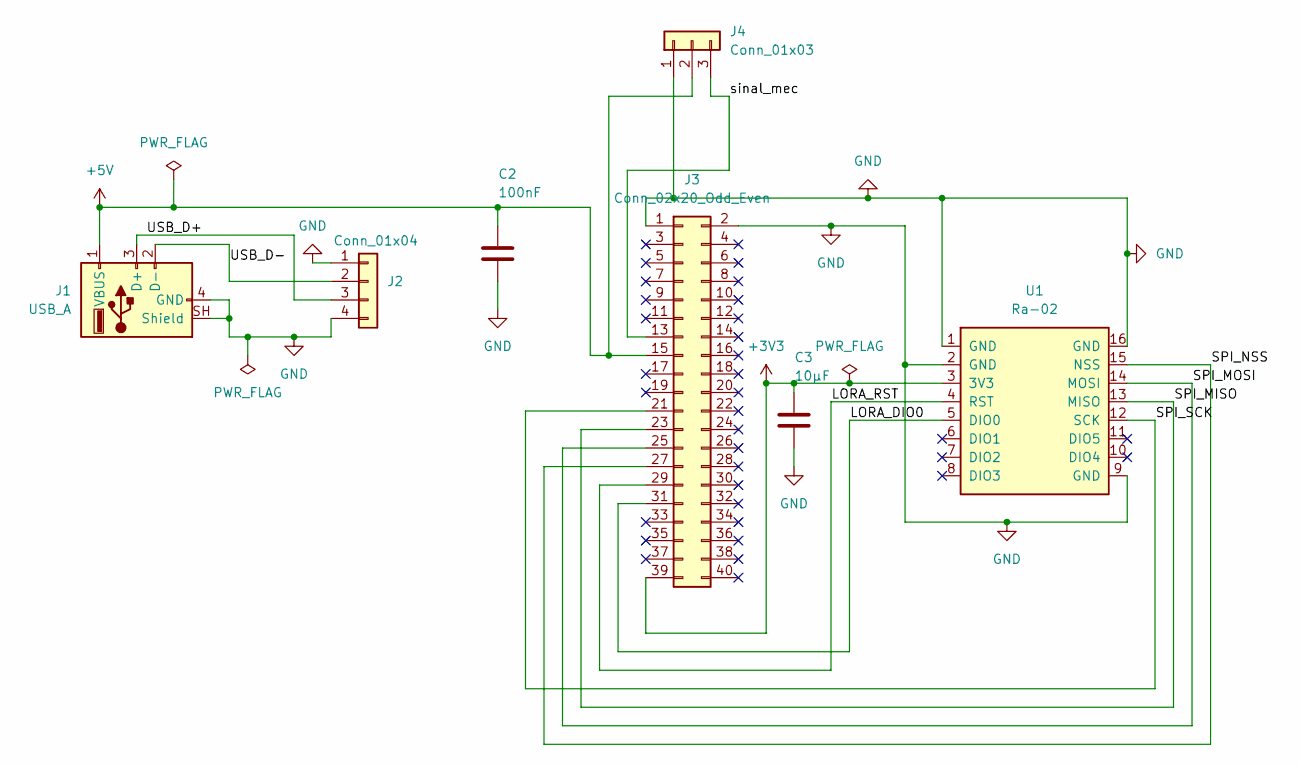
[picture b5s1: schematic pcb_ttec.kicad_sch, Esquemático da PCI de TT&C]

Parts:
C2: 100nF; C_Disc_D5.0mm_W2.5mm_P5.00mm
C3: 10µF; CP_Radial_Tantal_D5.0mm_P2.50mm
J1: USB_A; USB_A_Molex_67643_Horizontal
J2: Conn_01x04; PadsFio_1x04
J3: Conn_02x20_Odd_Even; PinSocket_2x20_P2.54mm_Vertical
J4: Conn_01x03; JST_XH_B3B-XH-A_1x03_P2.50mm_Vertical
U1: Ra-02; Ra-02_Breakout_THT

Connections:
+3V3: C3.1, J3.39, U1.3 (3V3)
+5V: C2.1, J1.1 (VBUS), J3.15, J4.2
/LORA_DIO0: J3.31, U1.5 (DIO0)
/LORA_RST: J3.29, U1.4 (RST)
/SPI_MISO: J3.23, U1.13 (MISO)
/SPI_MOSI: J3.25, U1.14 (MOSI)
/SPI_NSS: J3.27, U1.15 (NSS)
/SPI_SCK: J3.21, U1.12 (SCK)
/USB_D+: J1.3 (D+), J2.3
/USB_D-: J1.2 (D-), J2.2
/sinal_mec: J3.13, J4.3
GND: C2.2, C3.2, J1.4 (GND), J1.SH (Shield), J2.1, J2.4, J3.1, J3.2, J4.1, U1.1 (GND), U1.2 (GND), U1.9 (GND), U1.16 (GND)

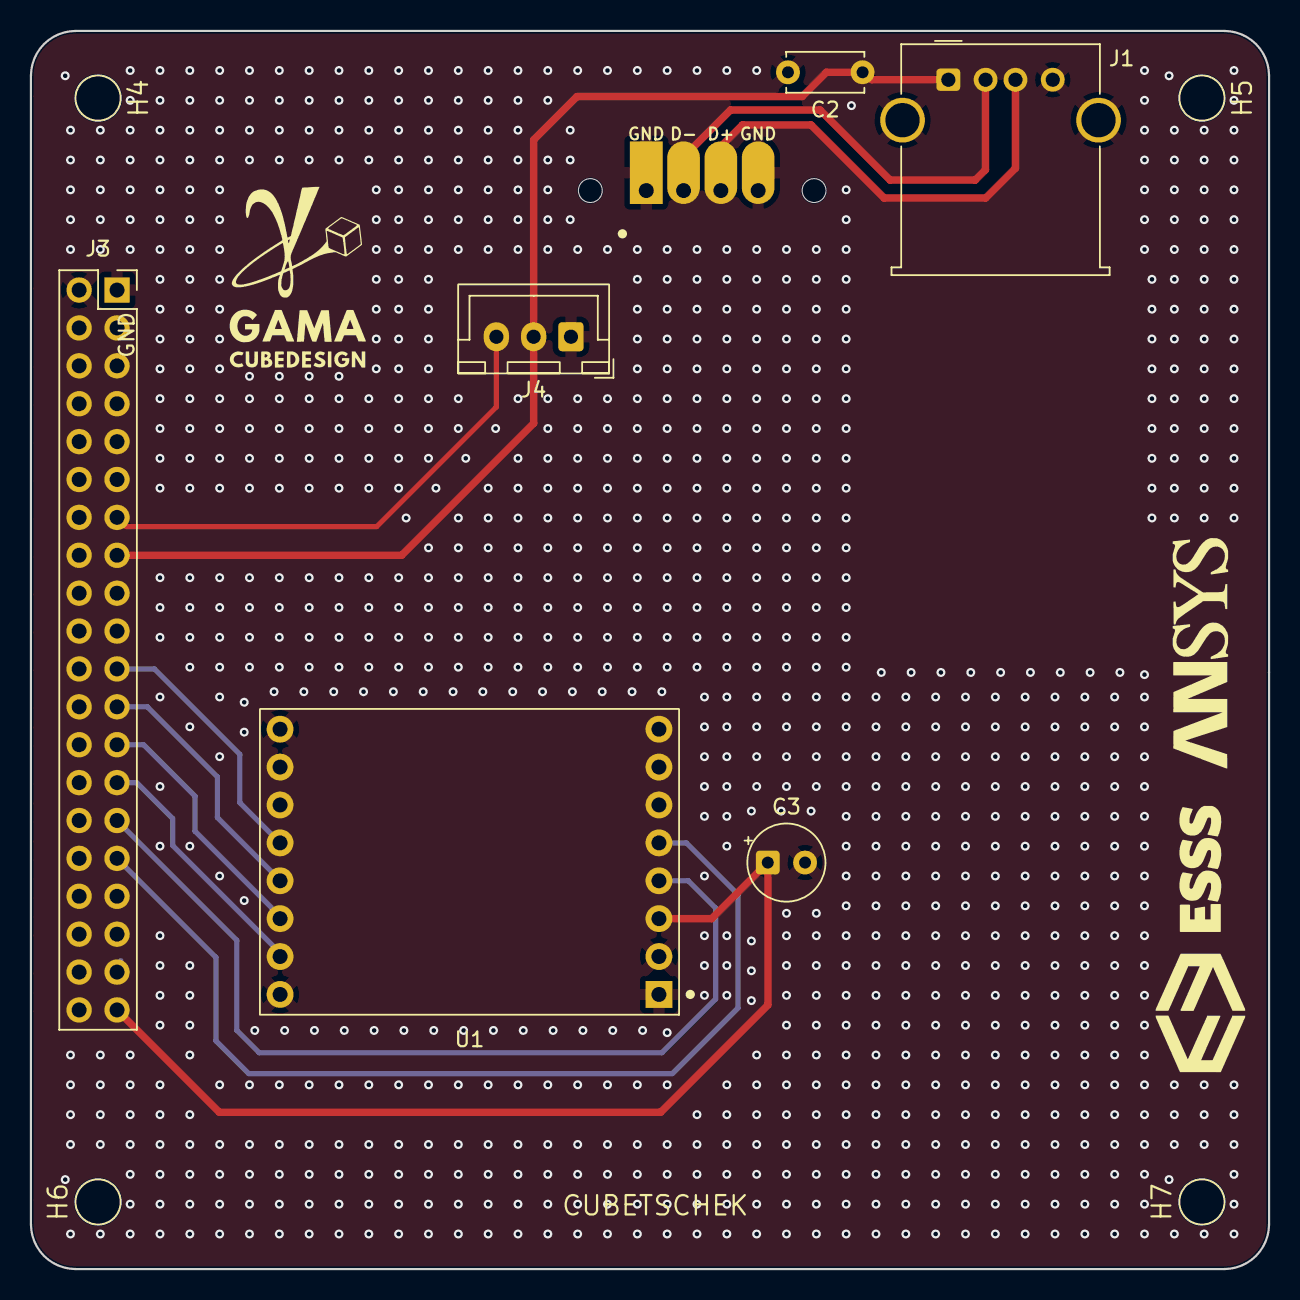
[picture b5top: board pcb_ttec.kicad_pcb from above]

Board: 2 copper layers, 83.0 x 83.0 mm, 13 parts (0 on the bottom side), 12 nets.

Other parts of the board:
H4, H5, H6, H7: MountingHole_3.20mm
LOGO2: ESSS_ANSYS; Logo_ESSS_ANSYS
logo: LOGO; Logo
